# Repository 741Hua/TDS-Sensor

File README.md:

# TDS-Sensor
The industrial Total Dissolved Solids (TDS) sensor market currently sells sensors as a two part solution: an Electrical Conductivity (EC) sensor probe and a separate box with the digitization hardware. Introducing, an all-in-one enclosure, plug and play, industrial TDS sensor intended for use in food &amp; beverage manufacturing facilities.

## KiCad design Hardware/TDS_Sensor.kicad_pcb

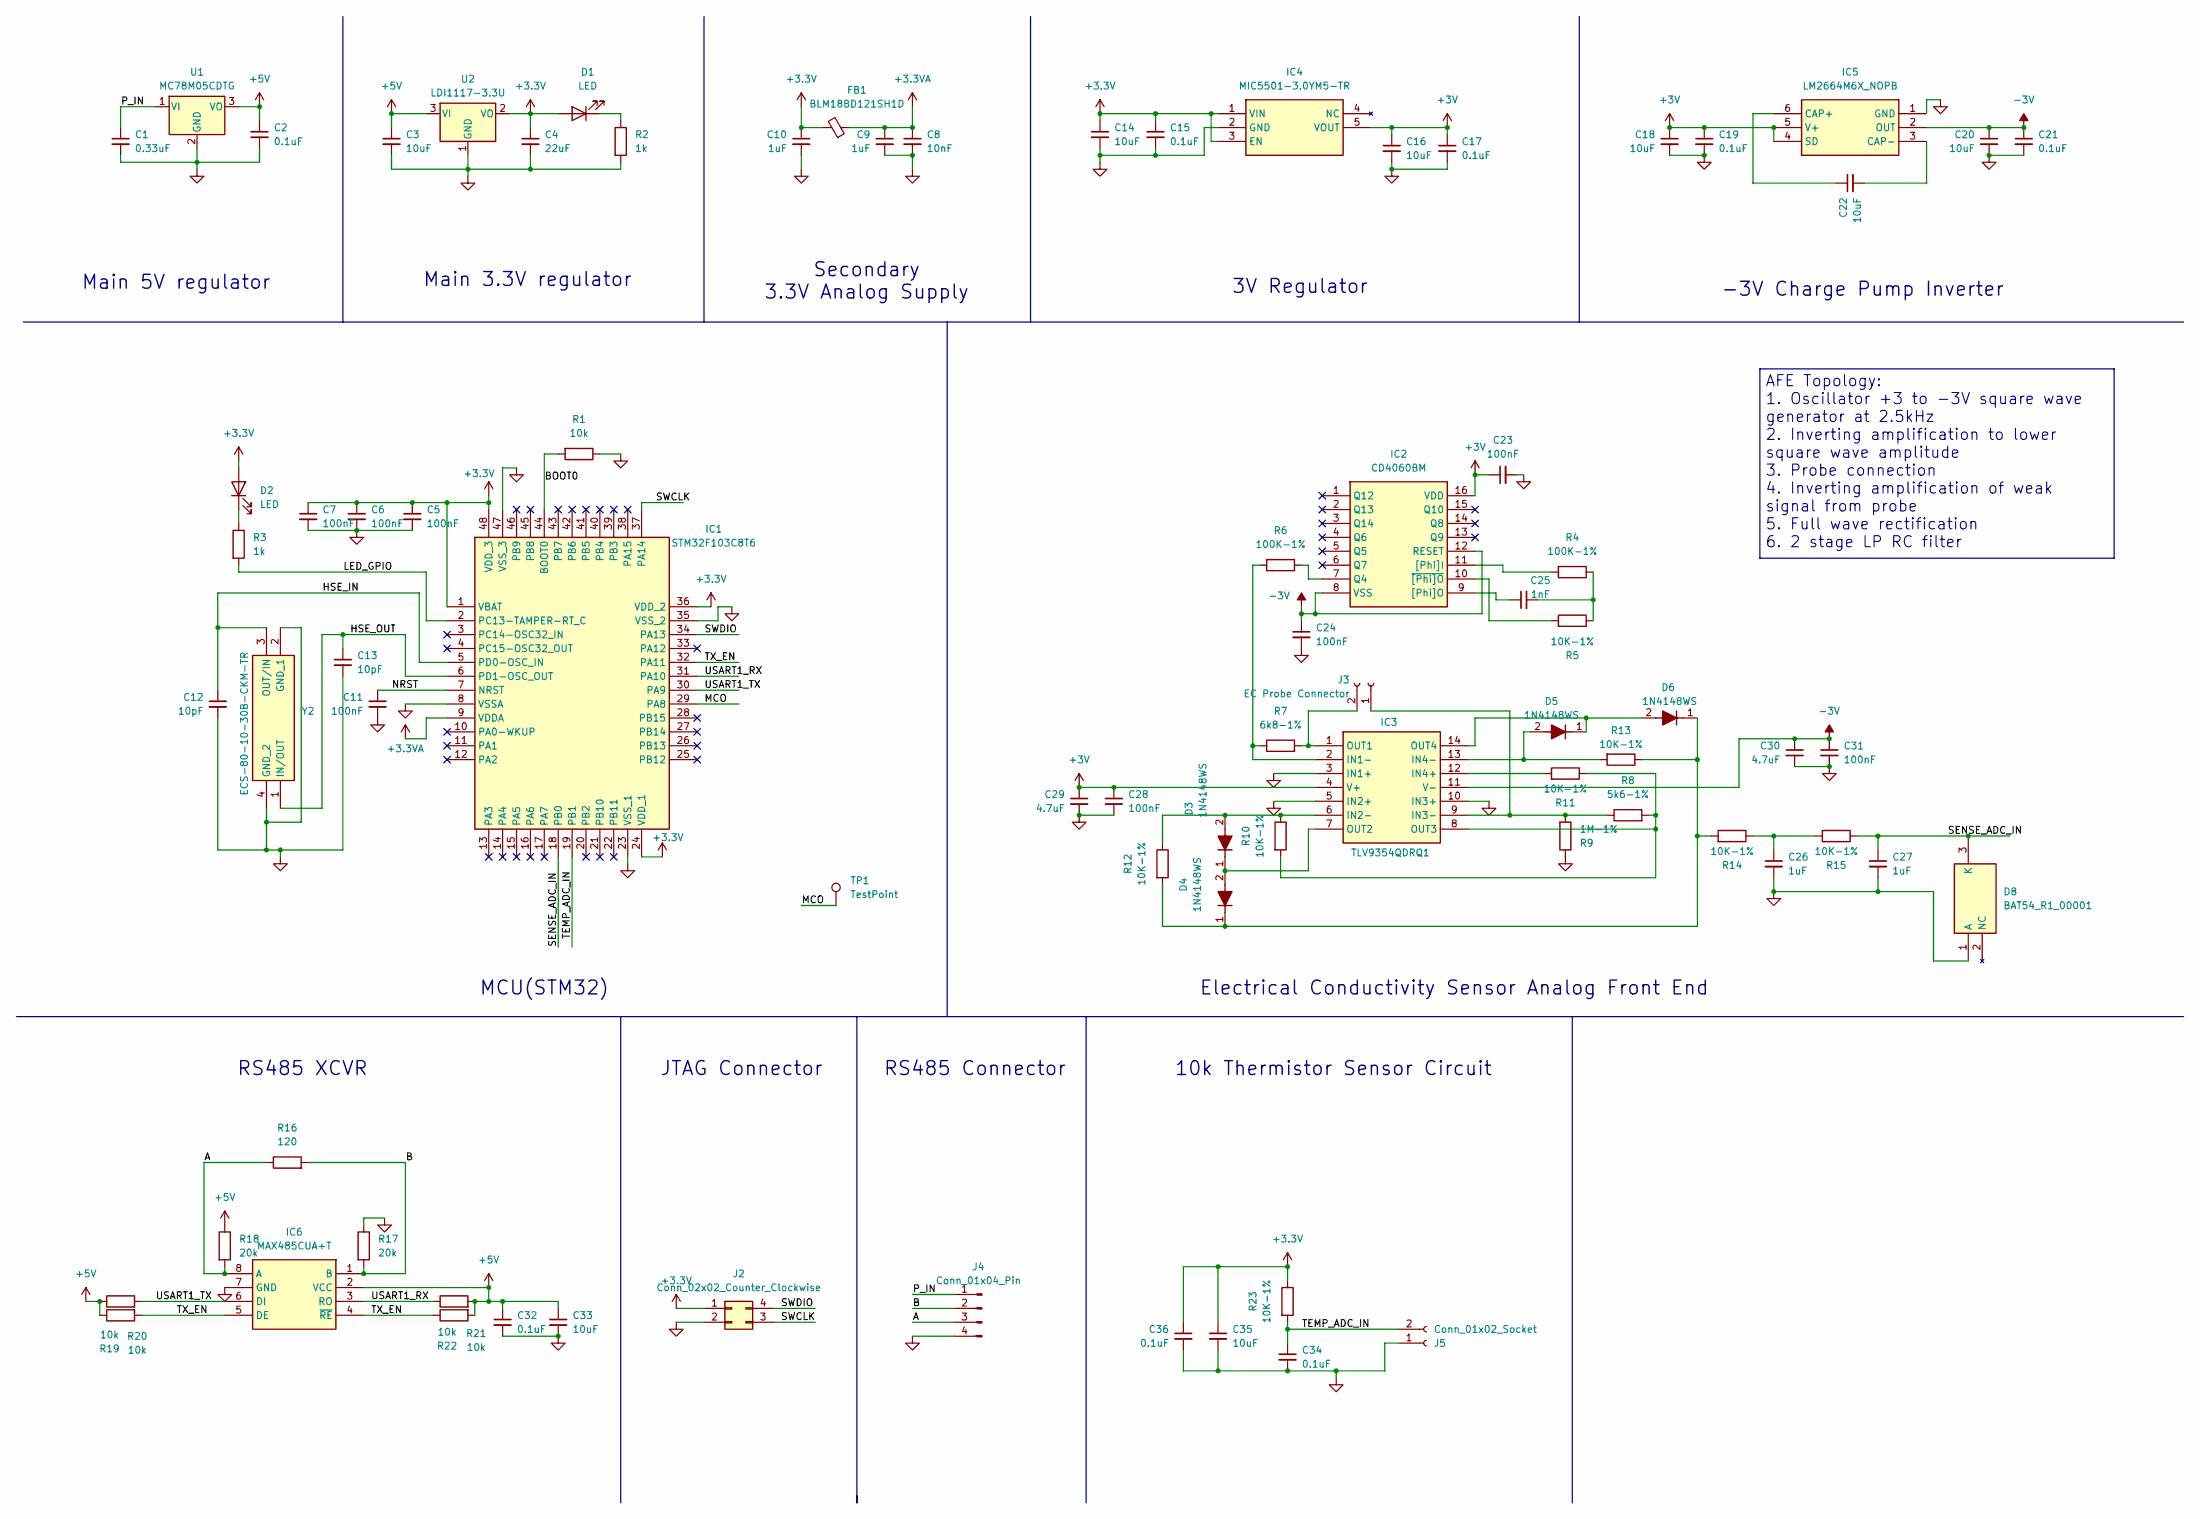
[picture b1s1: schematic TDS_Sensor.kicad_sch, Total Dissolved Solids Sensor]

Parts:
C1: 0.33uF; C_0603_1608Metric_Pad1.08x0.95mm_HandSolder; Manufacturer_Part_Number 0603B334K160CT
C2, C15, C17, C19, C21, C32, C34, C36: 0.1uF; C_0603_1608Metric_Pad1.08x0.95mm_HandSolder; Manufacturer_Part_Number 885012206095
C3, C14, C16, C18, C20, C22, C33, C35: 10uF; C_0603_1608Metric_Pad1.08x0.95mm_HandSolder; Manufacturer_Part_Number CL10A106KQ8NNNL
C4: 22uF; C_0603_1608Metric_Pad1.08x0.95mm_HandSolder; Manufacturer_Part_Number GRM188R61A226ME15D
C5, C6, C7, C11, C23, C24, C28, C31: 100nF; C_0603_1608Metric_Pad1.08x0.95mm_HandSolder; Manufacturer_Part_Number 885012206095
C8: 10nF; C_0603_1608Metric_Pad1.08x0.95mm_HandSolder; Manufacturer_Part_Number GRM188R72A103KA01J
C9, C10, C26, C27: 1uF; C_0603_1608Metric_Pad1.08x0.95mm_HandSolder; Manufacturer_Part_Number 0603B105K100CT
C12, C13: 10pF; C_0603_1608Metric_Pad1.08x0.95mm_HandSolder; Manufacturer_Part_Number 0603N100F500CT
C25: 1nF; C_0603_1608Metric_Pad1.08x0.95mm_HandSolder; Manufacturer_Part_Number CL10C102JB81PNC
C29, C30: 4.7uF; C_0603_1608Metric_Pad1.08x0.95mm_HandSolder; Manufacturer_Part_Number GRT188C80G475KE01D
D1, D2: LED; LEDC1608X90N; Manufacturer_Part_Number LTST-C190GKT
D3, D4, D5, D6: 1N4148WS; 1N4148WXLTP; Manufacturer_Part_Number 1N4148WS; Mouser Part Number 512-1N4148WS
D8: BAT54_R1_00001; SOT95P240X110-3N; Manufacturer_Part_Number BAT54_R1_00001; Mouser Part Number 241-BAT54_R1_00001
FB1: BLM18BD121SH1D; BLM18SP221SN1B; Manufacturer_Part_Number BLM18BD121SH1D
IC1: STM32F103C8T6; QFP50P900X900X160-48N; Manufacturer_Part_Number STM32F103C8T6; Mouser Part Number 511-STM32F103C8T6
IC2: CD4060BM; SOIC127P600X175-16N; Manufacturer_Part_Number CD4060BM; Mouser Part Number 595-CD4060BM
IC3: TLV9354QDRQ1; SOIC127P600X175-14N; Mouser Part Number 595-TLV9354QDRQ1
IC4: MIC5501-3.0YM5-TR; SOT95P280X145-5N; Manufacturer_Part_Number MIC5501-3.0YM5-TR; Mouser Part Number 998-MIC5501-3.0YM5TR
IC5: LM2664M6X_NOPB; SOT95P280X145-6N; Manufacturer_Part_Number LM2664M6X/NOPB; Mouser Part Number 926-LM2664M6X/NOPB
IC6: MAX485CUA+T; SOP65P490X110-8N; Manufacturer_Part_Number MAX485CUA+T; Mouser Part Number 700-MAX485CUAT
J2: Conn_02x02_Counter_Clockwise; PinHeader_2x02_P2.54mm_Vertical
J3: EC Probe Connector; HDRRA2W64P0X254_1X2_508X250X288P; Manufacturer_Part_Number PH1RB-02-UA
J4: Conn_01x04_Pin; Custom_Wire_Solder_Pad_4POS
J5: Conn_01x02_Socket; HDRRA2W64P0X254_1X2_508X250X288P; Manufacturer_Part_Number PH1RB-02-UA
R1, R19, R20, R21, R22: 10k; R_0603_1608Metric_Pad0.98x0.95mm_HandSolder; Manufacturer_Part_Number RK73H1JTTDD1002F
R2, R3: 1k; R_0603_1608Metric_Pad0.98x0.95mm_HandSolder; Manufacturer_Part_Number CRGCQ0603F1K0
R4, R6: 100K-1%; R_0603_1608Metric_Pad0.98x0.95mm_HandSolder; Manufacturer_Part_Number WR06X1003FTL
R5, R10, R11, R12, R13, R14, R15, R23: 10K-1%; R_0603_1608Metric_Pad0.98x0.95mm_HandSolder; Manufacturer_Part_Number RK73H1JTTDD1002F
R7: 6k8-1%; R_0603_1608Metric_Pad0.98x0.95mm_HandSolder; Manufacturer_Part_Number CRG0603F6K8
R8: 5k6-1%; R_0603_1608Metric_Pad0.98x0.95mm_HandSolder; Manufacturer_Part_Number CRGH0603F5K6
R9: 1M-1%; R_0603_1608Metric_Pad0.98x0.95mm_HandSolder; Manufacturer_Part_Number CR0603-FX-1004ELF
R16: 120; R_0603_1608Metric_Pad0.98x0.95mm_HandSolder; Manufacturer_Part_Number RC0603FR-07120RL
R17, R18: 20k; R_0603_1608Metric_Pad0.98x0.95mm_HandSolder; Manufacturer_Part_Number RK73H1JTTDD2002F
TP1: TestPoint; TestPoint_Pad_D1.0mm
U1: MC78M05CDTG; TO-252-2; Manufacturer_Part_Number MC78M05CDTG
U2: LDI1117-3.3U; SOT-89-3_Handsoldering; Manufacturer_Part_Number LDI1117-3.3U
Y2: ECS-80-10-30B-CKM-TR; ECS801030BCKMTR; Manufacturer_Part_Number ECS-80-10-30B-CKM-TR; Mouser Part Number 520-80-10-30B-CKM-TR

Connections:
+3.3V: C4.1, C5.1, C6.1, C7.1, C10.1, C14.1, C15.1, C35.1, C36.1, D1.2 (A), D2.2 (A), FB1.2, IC1.1 (VBAT), IC1.24 (VDD_1), IC1.36 (VDD_2), IC1.48 (VDD_3), IC4.1 (VIN), IC4.3 (EN), J2.1, R23.1, U2.2 (VO)
+3.3VA: C8.1, C9.1, FB1.1, IC1.9 (VDDA)
+3V: C16.1, C17.1, C18.1, C19.1, C23.1, C28.1, C29.1, IC2.16 (VDD), IC3.4 (V+), IC4.5 (VOUT), IC5.4 (SD), IC5.5 (V+)
+5V: C2.1, C3.1, C32.1, C33.1, IC6.2 (VCC), R18.1, R19.1, R20.1, R21.2, R22.2, U1.3 (VO), U2.3 (VI)
-3V: C20.1, C21.1, C24.1, C30.1, C31.1, IC2.8 (VSS), IC2.12 (RESET), IC3.11 (V-), IC5.2 (OUT)
/A: IC6.8 (A), J4.3, R16.1, R18.2
/B: IC6.1 (B), J4.2, R16.2, R17.2
/BOOT0: IC1.44 (BOOT0), R1.2
/HSE_IN: C12.1, IC1.5 (PD0-OSC_IN), Y2.3 (OUT/IN)
/HSE_OUT: C13.1, IC1.6 (PD1-OSC_OUT), Y2.1 (IN/OUT)
/LED_GPIO: IC1.2 (PC13-TAMPER-RT_C), R3.2
/MCO: IC1.29 (PA8), TP1.1 (1_1)
/NRST: C11.1, IC1.7 (NRST)
/P_IN: C1.1, J4.1, U1.1 (VI)
/SENSE_ADC_IN: C27.1, D8.3 (K), IC1.18 (PB0), R15.1
/SWCLK: IC1.37 (PA14), J2.3
/SWDIO: IC1.34 (PA13), J2.4
/TEMP_ADC_IN: C34.1, IC1.19 (PB1), J5.2, R23.2
/TX_EN: IC1.32 (PA11), IC6.4 (~RE), IC6.5 (DE), R19.2, R22.1
/USART1_RX: IC1.31 (PA10), IC6.3 (RO), R21.1
/USART1_TX: IC1.30 (PA9), IC6.6 (DI), R20.2
GND: C1.2, C2.2, C3.2, C4.2, C5.2, C6.2, C7.2, C8.2, C9.2, C10.2, C11.2, C12.2, C13.2, C14.2, C15.2, C16.2, C17.2, C18.2, C19.2, C20.2, C21.2, C23.2, C24.2, C26.2, C27.2, C28.2, C29.2, C30.2, C31.2, C32.2, C33.2, C34.2, C35.2, C36.2, D8.1 (A), IC1.8 (VSSA), IC1.23 (VSS_1), IC1.35 (VSS_2), IC1.47 (VSS_3), IC3.3 (IN1+), IC3.5 (IN2+), IC3.10 (IN3+), IC4.2 (GND), IC5.1 (GND), IC6.7 (GND), J2.2, J4.4, J5.1, R1.1, R2.2, R9.1, R17.1, U1.2 (GND), U2.1 (GND), Y2.2 (GND_1), Y2.4 (GND_2)
unnamed: C25.2, R4.1, R5.1
unnamed: C26.1, R14.1, R15.2
unnamed: D1.1 (K), R2.1
unnamed: D2.1 (K), R3.1
unnamed: D3.2 (A), IC3.6 (IN2-), R10.1, R12.1
unnamed: D3.1 (K), D4.2 (A), IC3.7 (OUT2)
unnamed: D4.1 (K), D6.1 (K), R12.2, R13.1, R14.2
unnamed: D5.2 (A), IC3.13 (IN4-), R13.2
unnamed: D5.1 (K), D6.2 (A), IC3.14 (OUT4)
unnamed: IC2.7 (Q4), R6.1
unnamed: IC2.11 ([Phi]I), R4.2
unnamed: C25.1, IC2.9 ([Phi]O)
unnamed: IC2.10 (~[Phi]O), R5.2
unnamed: IC3.2 (IN1-), R6.2, R7.1
unnamed: IC3.9 (IN3-), J3.1, R8.1, R9.2
unnamed: IC3.12 (IN4+), R11.2
unnamed: IC3.1 (OUT1), J3.2, R7.2
unnamed: IC3.8 (OUT3), R8.2, R10.2, R11.1
unnamed: C22.1, IC5.6 (CAP+)
unnamed: C22.2, IC5.3 (CAP-)

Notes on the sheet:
10k Thermistor Sensor Circuit
Main 3.3V regulator
RS485 XCVR
MCU(STM32)
-3V Charge Pump Inverter
JTAG Connector
Secondary 3.3V Analog Supply
3V Regulator
RS485 Connector
Main 5V regulator
Electrical Conductivity Sensor Analog Front End
AFE Topology: 1. Oscillator +3 to -3V square wave generator at 2.5kHz 2. Inverting amplification to lower square wave amplitude 3. Probe connection 4. Inverting amplification of weak signal from probe 5. Full wave rectification 6. 2 stage LP RC filter

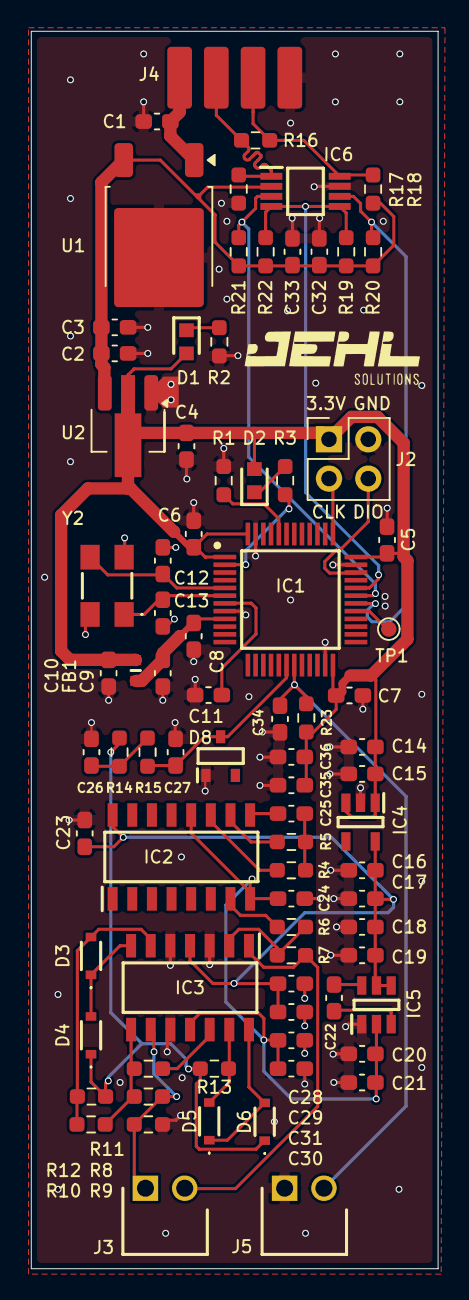
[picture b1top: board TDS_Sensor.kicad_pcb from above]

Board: 4 copper layers, 26.3 x 80.0 mm, 81 parts (0 on the bottom side), 42 nets.

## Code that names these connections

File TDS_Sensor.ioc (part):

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Mcu.Name=STM32F103C(8-B)Tx
Mcu.Package=LQFP48
Mcu.UserName=STM32F103C8Tx
PA10.Mode=Asynchronous
PA10.Signal=USART1_RX
PA13.Mode=Serial_Wire
PA13.Signal=SYS_JTMS-SWDIO
PA14.Mode=Serial_Wire
PA14.Signal=SYS_JTCK-SWCLK
PA8.GPIOParameters=GPIO_Label
PA8.GPIO_Label=TX_EN
PA8.Signal=GPIO_Output
PA9.Mode=Asynchronous
PA9.Signal=USART1_TX
PB0.Signal=ADCx_IN8
PC13-TAMPER-RTC.Signal=GPIO_Output
PD0-OSC_IN.Mode=HSE-External-Oscillator
PD0-OSC_IN.Signal=RCC_OSC_IN
PD1-OSC_OUT.Mode=HSE-External-Oscillator
PD1-OSC_OUT.Signal=RCC_OSC_OUT
RCC.SYSCLKFreq_VALUE=72000000
RCC.SYSCLKSource=RCC_SYSCLKSOURCE_PLLCLK
board=custom
